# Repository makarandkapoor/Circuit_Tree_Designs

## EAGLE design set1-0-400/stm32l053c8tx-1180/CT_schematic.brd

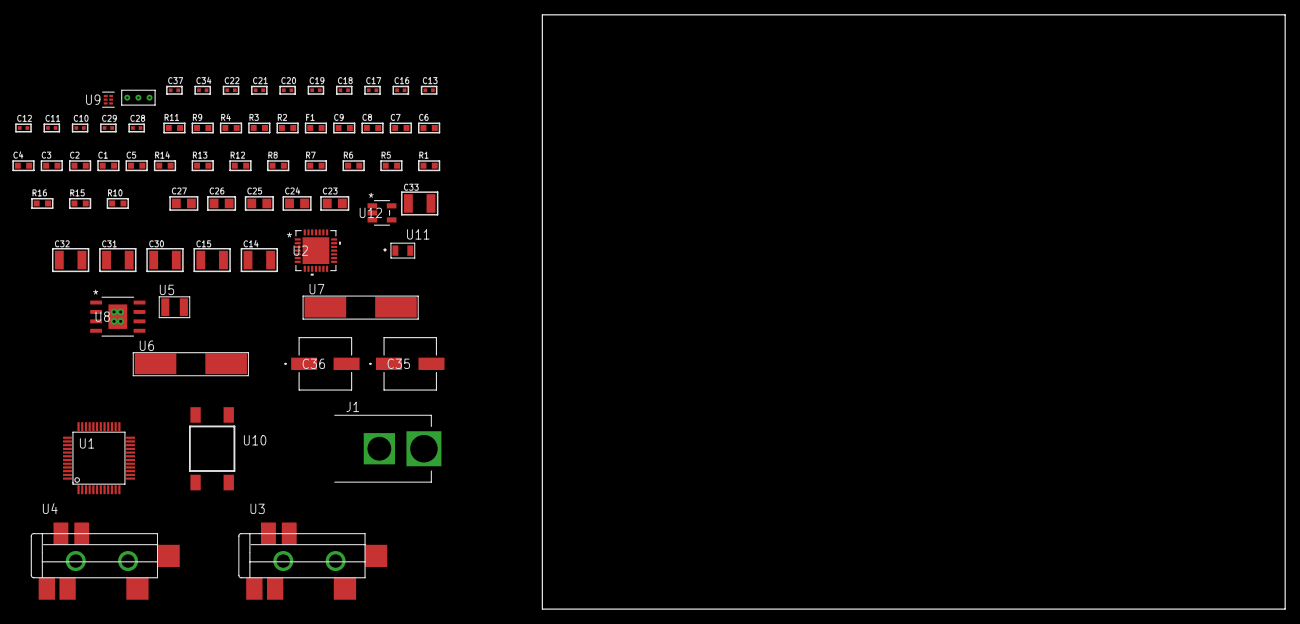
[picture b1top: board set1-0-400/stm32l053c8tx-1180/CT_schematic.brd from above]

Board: 2 copper layers, 100.0 x 80.0 mm, 68 parts (0 on the bottom side), 29 nets, no tracks yet.

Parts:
C1, C2, C3, C4, C6, C9: 1e-07; C0603
C5: 4.7e-06; C0603
C7: 1e-08; C0603
C8: 1e-06; C0603
C10, C11, C12, C13: 1e-11; C0402
C14, C15: 2.2e-05; C1210
C16, C17: 1e-09; C0402
C18, C19, C20, C21, C22, C34: 1e-07; C0402
C23, C24, C25, C26, C27: 1e-05; C0805
C28, C29: 2.2e-11; C0402
C30, C31, C32, C33: 1e-05; C1210
C35, C36: 0.0001; EXV-9H
C37: 1e-08; C0402
F1: 240.0; L0603
J1: PJ-037B; PJ-037B_PACKAGE
R1, R5, R12, R13: 10000.0; R0603
R2: 1000.0; R0603
R3: 910.0; R0603
R4: 4700.0; R0603
R6, R7, R8: 47000.0; R0603
R9: 680.0; R0603
R10: 1402.2764227642; R0603
R11: 2200.0; R0603
R14: 82000.0; R0603
R15: 300000.0; R0603
R16: 120000.0; R0603
U1: STM32L053C8T7; LQFP48
U2: WM8731CLSEFL; QFN-28
U3, U4: SJ-43515TS-SMT-TR
U5: ABS07-32.768KHZ-7-T
U6: ABLS-25.000MHZ-B2F-T
U7: ABLS-12.288MHZ-B4-T
U8: MIC5234YME; SOIC-8_EP
U9: TPS3895ADRYR; SON-6
U10: 4-1437565-2; SW_4-1437565-2
U11: Q65110A2395; LGM67K-G1J2-24-Z
U12: nc7sz125m5x; NC7SZ125M5X
U13: Dummy; DUMMY_PACKAGE_130

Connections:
CLK_CRYSTAL_U1_3: C10.1, U1.3, U5.1
CLK_CRYSTAL_U1_4: C11.1, U1.4, U5.2
CLK_CRYSTAL_U1_5: C12.1, U1.5, U6.1
CLK_CRYSTAL_U1_6: C13.1, U1.6, U6.2
CLK_CRYSTAL_U2_1: C28.1, U2.1, U7.1
CLK_CRYSTAL_U2_2: C29.1, U2.2, U7.2
GND: C1.2, C2.2, C3.2, C4.2, C5.2, C6.2, C7.2, C8.2, C9.2, C10.2, C11.2, C12.2, C13.2, C17.2, C18.2, C19.2, C20.2, C21.2, C22.2, C23.2, C24.2, C25.2, C26.2, C27.2, C28.2, C29.2, C30.2, C31.2, C32.2, C33.2, C34.2, C35.2, C36.2, C37.2, J1.2, R2.2, R5.2, R6.2, R7.2, R8.2, R11.2, R14.2, R16.2, U1.8, U1.23, U1.35, U1.47, U2.4, U2.15, U2.19, U2.25, U2.26, U2.29, U3.1, U4.1, U8.7, U8.EPAD, U9.2, U11.C, U12.1, U12.3, U13.1
NET_U1_1: C6.1, U1.1
NET_U1_7: R4.1, U1.7, U12.4
NET_U1_9: C7.1, C8.1, F1.1, U1.9
NET_U1_44: R5.1, U1.44
NET_U1_45: R3.1, U1.45, U11.A
NET_U1_46: R1.1, U1.46, U10.3, U10.4
NET_U2_20: C22.1, C27.1, U2.20
NET_U3_2: C15.1, R7.1, U3.2
NET_U3_5: C14.1, R6.1, U3.5
NET_U4_5: C16.1, C17.1, R8.1, R9.1, U4.5
NET_U8_4: R10.2, R11.1, U8.4
NET_U9_1: R13.1, R14.1, U9.1
NET_U9_3: R15.2, R16.1, U9.3
NET_U9_4: R12.1, U9.4, U12.2
NET_U10_1: R2.1, U10.1, U10.2
PROC_I2S2_CK: U1.26, U2.7
PROC_I2S2_SD: U1.28, U2.8
PROC_I2S2_WS: U1.25, U2.9, U2.11
PROC_TIM2_CH1: U1.10, U13.3
PROC_TIM2_CH3: U1.12, U13.2
VCC_S1_4V6: C30.1, C31.1, C35.1, C36.1, J1.1, U8.5, U8.8
VCC_TIER1_1V8: C1.1, C2.1, C3.1, C4.1, C5.1, C9.1, C18.1, C19.1, C20.1, C21.1, C23.1, C24.1, C25.1, C26.1, C32.1, C33.1, C34.1, C37.1, F1.2, R1.2, R3.2, R4.2, R10.1, R12.2, R13.2, R15.1, U1.24, U1.36, U1.48, U2.3, U2.5, U2.12, U2.18, U8.1, U9.6, U12.5

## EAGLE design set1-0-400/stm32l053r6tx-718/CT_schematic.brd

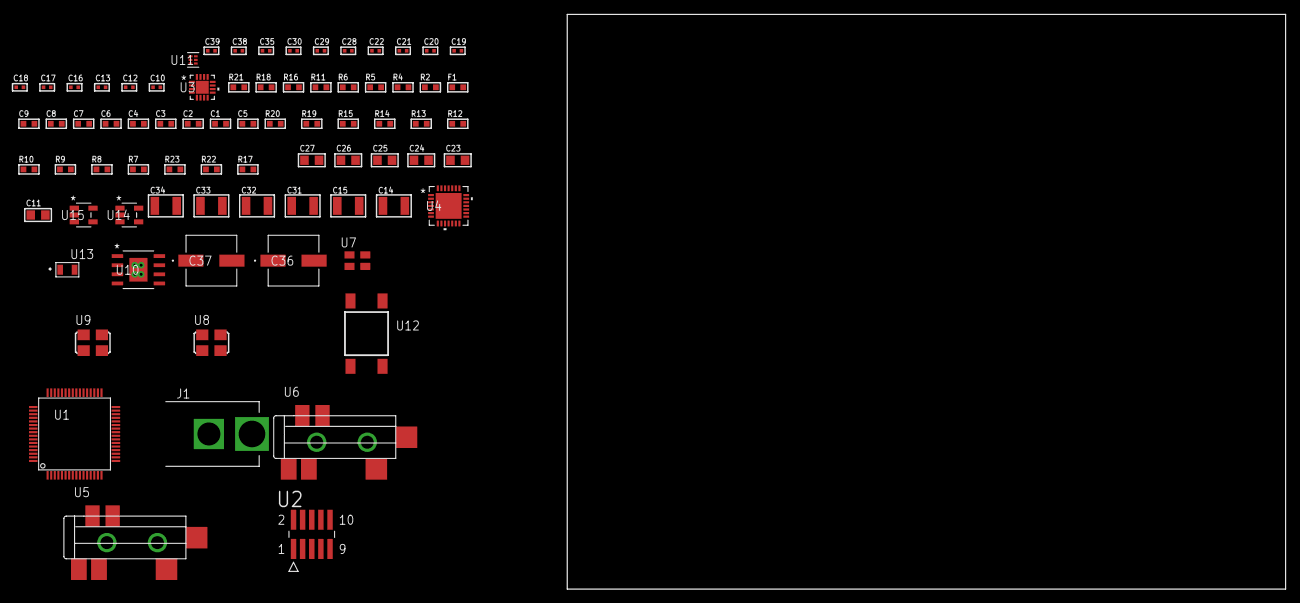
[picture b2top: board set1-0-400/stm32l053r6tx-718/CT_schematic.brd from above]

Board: 2 copper layers, 100.0 x 80.0 mm, 77 parts (0 on the bottom side), 31 nets, no tracks yet.

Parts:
C1, C2, C3, C4, C6, C9: 1e-07; C0603
C5: 4.7e-06; C0603
C7: 1e-08; C0603
C8: 1e-06; C0603
C10, C12, C13, C18, C19, C20, C21, C22, C35: 1e-07; C0402
C11: 4.7e-06; C0805
C14, C15: 2.2e-05; C1210
C16, C17: 1e-09; C0402
C23, C24, C25, C26, C27: 1e-05; C0805
C28, C29, C30, C38, C39: 1e-08; C0402
C31, C32, C33, C34: 1e-05; C1210
C36, C37: 0.0001; EXV-9H
F1: 240.0; L0603
J1: PJ-037B; PJ-037B_PACKAGE
R2: 1000.0; R0603
R4: 4700.0; R0603
R5, R6, R18: 2200.0; R0603
R7, R8, R9, R10, R12, R19, R20: 10000.0; R0603
R11: 5.0; R0603
R13, R14, R15: 47000.0; R0603
R16: 680.0; R0603
R17: 4031.5447154472; R0603
R21: 9100.0; R0603
R22: 680000.0; R0603
R23: 120000.0; R0603
U1: STM32L053R6T6; LQFP64
U2: FTSH-105-01-L-DV-K; SAMTEC_FTSH-105-01-L-DV-K
U3: MMA8451QT; QFN-16
U4: WM8731CLSEFL; QFN-28
U5, U6: SJ-43515TS-SMT-TR
U7: ASEK-32.768KHz-ECST; ASEK
U8: ASFL1-12.288MHZ-EC-T; ASFL1
U9: ASFL1-25MHZ-NCS; ASFL1
U10: MIC5234YME; SOIC-8_EP
U11: TPS3895ADRYR; SON-6
U12: 4-1437565-2; SW_4-1437565-2
U13: Q65110A2395; LGM67K-G1J2-24-Z
U14, U15: nc7sz125m5x; NC7SZ125M5X

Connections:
CLK_U1_3: U1.3, U7.3
CLK_U1_5: U1.5, U9.3
CLK_U4_1: U4.1, U8.3
GND: C1.2, C2.2, C3.2, C4.2, C5.2, C6.2, C7.2, C8.2, C9.2, C10.2, C11.2, C12.2, C13.2, C17.2, C18.2, C19.2, C20.2, C21.2, C22.2, C23.2, C24.2, C25.2, C26.2, C27.2, C28.2, C29.2, C30.2, C31.2, C32.2, C33.2, C34.2, C35.2, C36.2, C37.2, C38.2, C39.2, J1.2, R2.2, R7.2, R11.2, R13.2, R14.2, R15.2, R18.2, R21.2, R23.2, U1.12, U1.18, U1.31, U1.47, U1.63, U2.3, U2.5, U3.5, U3.10, U3.12, U3.17, U4.4, U4.15, U4.19, U4.25, U4.26, U4.29, U5.1, U6.1, U7.2, U8.2, U9.2, U10.7, U10.EPAD, U11.2, U13.C, U14.2, U14.3, U15.1, U15.3
NET_U1_1: C6.1, U1.1
NET_U1_7: R4.1, U1.7, U15.4
NET_U1_13: C7.1, C8.1, F1.1, U1.13
NET_U1_58: R5.1, U1.58, U3.4
NET_U1_59: R6.1, U1.59, U3.6
NET_U1_60: R7.1, U1.60
NET_U1_62: U12.3, U12.4
NET_U2_9: R11.1, U2.9
NET_U3_2: C13.1, U3.2
NET_U3_7: R12.1, U3.7
NET_U4_20: C22.1, C27.1, U4.20
NET_U5_2: C15.1, R14.1, U5.2
NET_U5_5: C14.1, R13.1, U5.5
NET_U6_5: C16.1, C17.1, R15.1, R16.1, U6.5
NET_U10_4: R17.2, R18.1, U10.4
NET_U11_1: R20.1, R21.1, U11.1
NET_U11_3: R22.2, R23.1, U11.3
NET_U11_4: R19.1, U11.4, U14.4, U15.2
NET_U12_1: R2.1, U12.1, U12.2
PROC_I2S2_CK: U1.34, U4.7
PROC_I2S2_SD: U1.11, U4.8
PROC_I2S2_WS: U1.33, U4.9, U4.11
PROC_SYS_SWCLK: R9.1, U1.49, U2.4
PROC_SYS_SWDIO: R10.1, U1.46, U2.2
RST_OUT_U2_JTAG_RST_B: R8.1, U2.10, U14.1
VCC_S1_13V3: C31.1, C32.1, C36.1, C37.1, J1.1, U10.5, U10.8
VCC_TIER1_3V3: C1.1, C2.1, C3.1, C4.1, C5.1, C9.1, C10.1, C11.1, C12.1, C18.1, C19.1, C20.1, C21.1, C23.1, C24.1, C25.1, C26.1, C28.1, C29.1, C30.1, C33.1, C34.1, C35.1, C38.1, C39.1, F1.2, R4.2, R5.2, R6.2, R8.2, R9.2, R10.2, R12.2, R17.1, R19.2, R20.2, R22.1, U1.19, U1.32, U1.48, U1.64, U2.1, U3.1, U3.14, U4.3, U4.5, U4.12, U4.18, U7.4, U8.4, U9.4, U10.1, U11.6, U14.5, U15.5

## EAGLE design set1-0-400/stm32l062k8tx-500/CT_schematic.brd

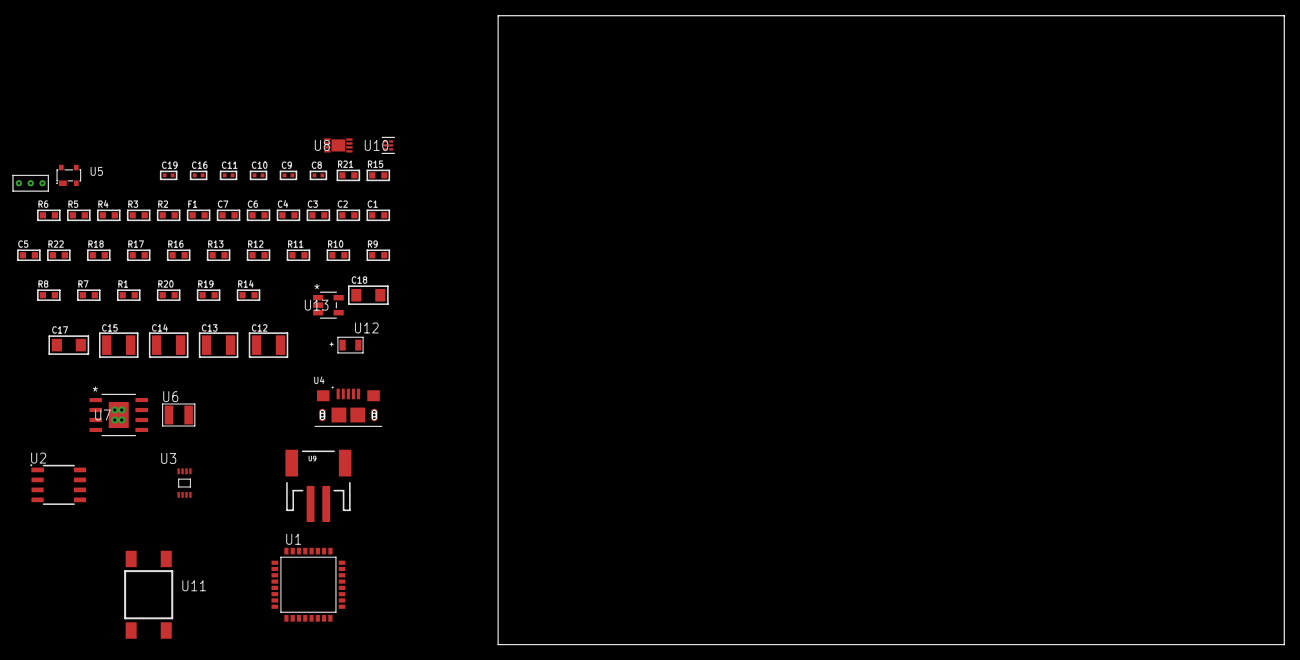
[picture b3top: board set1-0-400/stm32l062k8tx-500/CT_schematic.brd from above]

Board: 2 copper layers, 122.6 x 80.0 mm, 56 parts (0 on the bottom side), 33 nets, no tracks yet.

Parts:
C1, C2, C3, C4: 1e-07; C0603
C5: 4.7e-06; C0603
C6: 1e-08; C0603
C7: 1e-06; C0603
C8, C9: 1e-11; C0402
C10, C11, C19: 1e-08; C0402
C12, C13, C14, C15: 1e-05; C1210
C16: 1e-07; C0402
C17, C18: 1e-05; C1206
F1: 240.0; L0603
R1, R7, R8, R9, R10, R11, R12, R13, R16, R17, R22: 10000.0; R0603
R2: 1000.0; R0603
R3: 910.0; R0603
R4: 4700.0; R0603
R5, R6, R15: 2200.0; R0603
R14: 1402.2764227642; R0603
R18: 82000.0; R0603
R19: 300000.0; R0603
R20: 120000.0; R0603
R21: 2000.0; R0603
U1: STM32L062K8T6; LQFP32
U2: AT25080B-SSHL-T; SOIC-8
U3: 24AA128T-I/MNY; TDFN-8/6MM
U4: 10118193-0001LF; FCI_10118193-0001LF
U5: prtr5v0u2ax; SOT143B
U6: ABS07-32.768KHZ-7-T
U7: MIC5234YME; SOIC-8_EP
U8: MCP73831T-2ACI/MC; DFN8_2X3MC
U9: S2B-PH-SM4-TB(LF)(SN); JST-2-SMD
U10: TPS3895ADRYR; SON-6
U11: 4-1437565-2; SW_4-1437565-2
U12: Q65110A2395; LGM67K-G1J2-24-Z
U13: nc7sz125m5x; NC7SZ125M5X
U14: Dummy; DUMMY_PACKAGE_118

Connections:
CLK_CRYSTAL_U1_2: C8.1, U1.2, U6.1
CLK_CRYSTAL_U1_3: C9.1, U1.3, U6.2
GND: C1.2, C2.2, C3.2, C4.2, C5.2, C6.2, C7.2, C8.2, C9.2, C10.2, C11.2, C12.2, C13.2, C14.2, C15.2, C16.2, C17.2, C18.2, C19.2, R2.2, R7.2, R11.2, R15.2, R18.2, R20.2, R21.2, U1.16, U1.32, U2.4, U3.4, U4.5, U4.6, U4.7, U4.8, U4.9, U5.1, U7.7, U7.EPAD, U8.6, U8.9, U9.2, U10.2, U12.C, U13.1, U13.3, U14.1
INPUT_USBPOWER_5V: C17.1, R22.2, U4.1, U5.4, U8.1, U8.2
NET_U1_4: R4.1, U1.4, U13.4
NET_U1_5: C6.1, C7.1, F1.1, U1.5
NET_U1_27: R3.1, U1.27, U12.A
NET_U1_28: R1.1, U1.28, U11.3, U11.4
NET_U1_29: R5.1, U1.29, U3.6
NET_U1_30: R6.1, U1.30, U3.5
NET_U1_31: R7.1, U1.31
NET_U2_3: R8.1, U2.3
NET_U2_7: R10.1, U2.7
NET_U3_1: R11.1, U3.1
NET_U3_2: R12.1, U3.2
NET_U3_3: R13.1, U3.3
NET_U7_4: R14.2, R15.1, U7.4
NET_U8_5: R22.1, U8.5
NET_U8_8: R21.1, U8.8
NET_U10_1: R17.1, R18.1, U10.1
NET_U10_3: R19.2, R20.1, U10.3
NET_U10_4: R16.1, U10.4, U13.2
NET_U11_1: R2.1, U11.1, U11.2
PROC_PA0: U1.6, U14.2
PROC_PA1: U1.7, U14.3
PROC_SPI1_MISO: U1.12, U2.2
PROC_SPI1_MOSI: U1.13, U2.5
PROC_SPI1_NSS: R9.1, U1.10, U2.1
PROC_SPI1_SCK: U1.11, U2.6
PROC_USB_DM: U1.21, U4.2, U5.3
PROC_USB_DP: U1.22, U4.3, U5.2
VCC_S1_3V7: C12.1, C13.1, C18.1, U7.5, U7.8, U8.3, U8.4, U9.1
VCC_TIER1_1V8: C1.1, C2.1, C3.1, C4.1, C5.1, C10.1, C11.1, C14.1, C15.1, C16.1, C19.1, F1.2, R1.2, R3.2, R4.2, R5.2, R6.2, R8.2, R9.2, R10.2, R12.2, R13.2, R14.1, R16.2, R17.2, R19.1, U1.1, U1.17, U2.8, U3.7, U3.8, U7.1, U10.6, U13.5

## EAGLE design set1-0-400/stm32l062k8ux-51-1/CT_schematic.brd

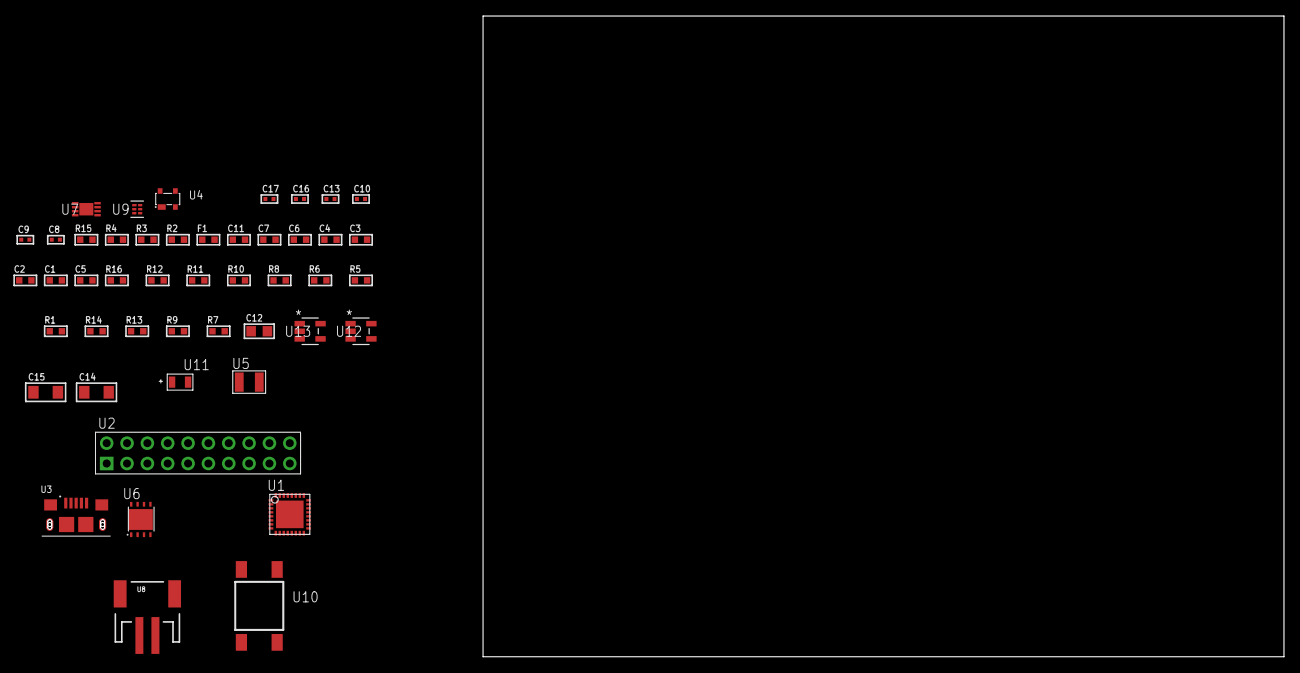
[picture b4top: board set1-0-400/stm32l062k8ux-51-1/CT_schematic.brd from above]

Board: 2 copper layers, 154.3 x 80.0 mm, 47 parts (0 on the bottom side), 24 nets, no tracks yet.

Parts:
C1, C2, C3, C4: 1e-07; C0603
C5: 4.7e-06; C0603
C6: 1e-08; C0603
C7, C11: 1e-06; C0603
C8, C9: 1e-11; C0402
C10, C13: 1e-07; C0402
C12: 1e-05; C0805
C14, C15: 1e-05; C1206
C16, C17: 1e-08; C0402
F1: 240.0; L0603
R1, R5, R6, R10, R11, R16: 10000.0; R0603
R2: 1000.0; R0603
R3: 910.0; R0603
R4: 4700.0; R0603
R7, R9: 100000.0; R0603
R8: 36000.0; R0603
R12: 82000.0; R0603
R13: 300000.0; R0603
R14: 120000.0; R0603
R15: 2000.0; R0603
U1: STM32L062K8U6; UFQFPN32
U2: TST-110-05-T-D-RA
U3: 10118193-0001LF; FCI_10118193-0001LF
U4: prtr5v0u2ax; SOT143B
U5: ABS07-32.768KHZ-7-T
U6: LP2951ACSDX/NOPB; WSON-8
U7: MCP73831T-2ACI/MC; DFN8_2X3MC
U8: S2B-PH-SM4-TB(LF)(SN); JST-2-SMD
U9: TPS3895ADRYR; SON-6
U10: 4-1437565-2; SW_4-1437565-2
U11: Q65110A2395; LGM67K-G1J2-24-Z
U12, U13: nc7sz125m5x; NC7SZ125M5X

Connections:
CLK_CRYSTAL_U1_2: C8.1, U1.2, U5.1
CLK_CRYSTAL_U1_3: C9.1, U1.3, U5.2
GND: C1.2, C2.2, C3.2, C4.2, C5.2, C6.2, C7.2, C8.2, C9.2, C10.2, C11.2, C12.2, C13.2, C14.2, C15.2, C16.2, C17.2, R2.2, R5.2, R9.2, R12.2, R14.2, R15.2, U1.EPAD, U2.4, U2.6, U2.8, U2.10, U2.12, U2.14, U2.16, U2.18, U2.20, U3.5, U3.6, U3.7, U3.8, U3.9, U4.1, U6.3, U6.4, U6.PAD, U7.6, U7.9, U8.2, U9.2, U11.C, U12.2, U12.3, U13.1, U13.3
INPUT_USBPOWER_5V: C14.1, R16.2, U3.1, U4.4, U7.1, U7.2
NET_U1_4: R4.1, U1.4, U13.4
NET_U1_5: C6.1, C7.1, F1.1, U1.5
NET_U1_30: R3.1, U1.30, U11.A
NET_U1_31: R5.1, U1.31
NET_U1_32: R1.1, U1.32, U10.3, U10.4
NET_U6_5: R7.1, U6.5
NET_U6_7: R8.2, R9.1, U6.7
NET_U7_5: R16.1, U7.5
NET_U7_8: R15.1, U7.8
NET_U9_1: R11.1, R12.1, U9.1
NET_U9_3: R13.2, R14.1, U9.3
NET_U9_4: R10.1, U9.4, U12.4, U13.2
NET_U10_1: R2.1, U10.1, U10.2
PROC_SYS_SWCLK: U1.24, U2.9
PROC_SYS_SWDIO: U1.23, U2.7
PROC_USB_DM: U1.21, U3.2, U4.3
PROC_USB_DP: U1.22, U3.3, U4.2
RST_OUT_U2_SRESET_B: R6.1, U2.15, U12.1
VCC_S1_3V7: C11.1, C15.1, U6.8, U7.3, U7.4, U8.1
VCC_TIER1_1V8: C1.1, C2.1, C3.1, C4.1, C5.1, C10.1, C12.1, C13.1, C16.1, C17.1, F1.2, R1.2, R3.2, R4.2, R6.2, R7.2, R8.1, R10.2, R11.2, R13.1, U1.1, U1.17, U2.1, U6.1, U9.6, U12.5, U13.5

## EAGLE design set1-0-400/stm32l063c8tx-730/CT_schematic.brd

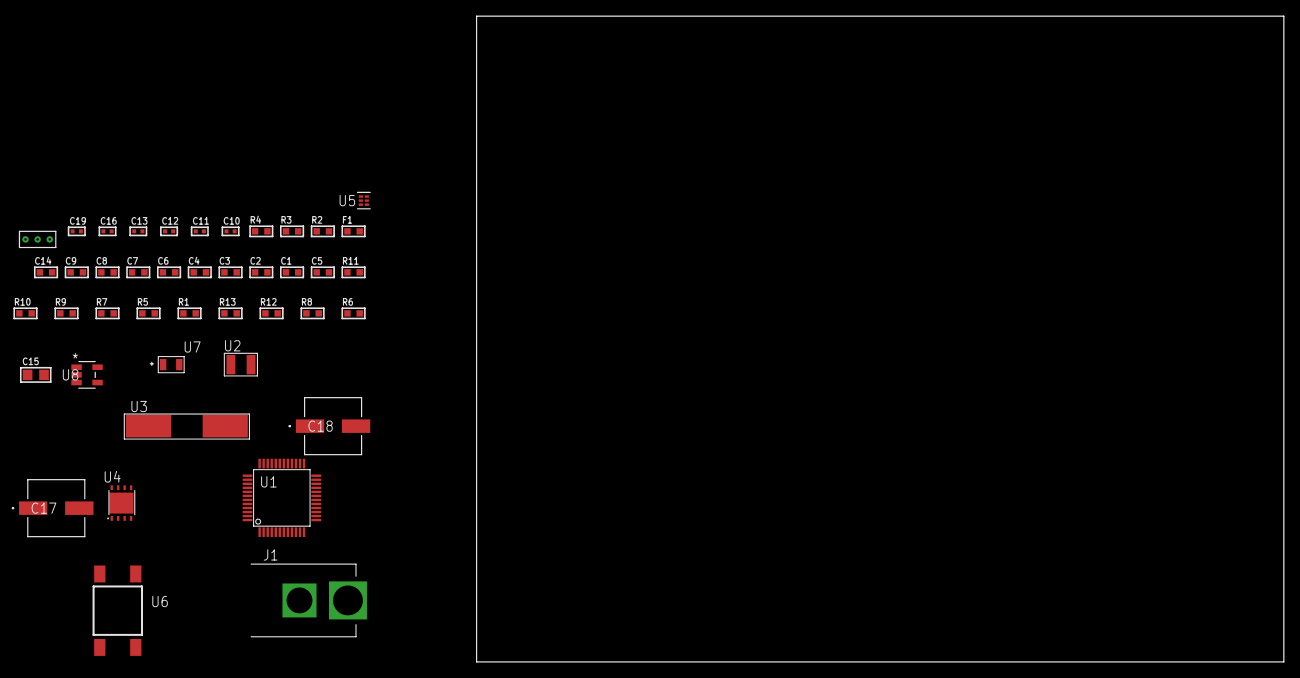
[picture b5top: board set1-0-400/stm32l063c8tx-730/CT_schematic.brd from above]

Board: 2 copper layers, 100.0 x 80.0 mm, 43 parts (0 on the bottom side), 21 nets, no tracks yet.

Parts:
C1, C2, C3, C4, C6, C9: 1e-07; C0603
C5: 4.7e-06; C0603
C7: 1e-08; C0603
C8: 1e-06; C0603
C10, C11, C12, C13: 1e-11; C0402
C14: 8e-07; R0603
C15: 1e-05; C0805
C16: 1e-07; C0402
C17, C18: 0.0001; EXV-9H
C19: 1e-08; C0402
F1: 240.0; L0603
J1: PJ-037B; PJ-037B_PACKAGE
R1, R5, R9, R10: 10000.0; R0603
R2: 1000.0; R0603
R3: 910.0; R0603
R4: 4700.0; R0603
R6, R8: 100000.0; R0603
R7: 36000.0; R0603
R11: 82000.0; R0603
R12: 300000.0; R0603
R13: 120000.0; R0603
U1: STM32L063C8T6; LQFP48
U2: ABS07-32.768KHZ-7-T
U3: ABLS-25.000MHZ-B2F-T
U4: LP2951ACSDX/NOPB; WSON-8
U5: TPS3895ADRYR; SON-6
U6: 4-1437565-2; SW_4-1437565-2
U7: Q65110A2395; LGM67K-G1J2-24-Z
U8: nc7sz125m5x; NC7SZ125M5X
U9: Dummy; DUMMY_PACKAGE_84

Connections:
CLK_CRYSTAL_U1_3: C10.1, U1.3, U2.1
CLK_CRYSTAL_U1_4: C11.1, U1.4, U2.2
CLK_CRYSTAL_U1_5: C12.1, U1.5, U3.1
CLK_CRYSTAL_U1_6: C13.1, U1.6, U3.2
GND: C1.2, C2.2, C3.2, C4.2, C5.2, C6.2, C7.2, C8.2, C9.2, C10.2, C11.2, C12.2, C13.2, C14.2, C15.2, C16.2, C17.2, C18.2, C19.2, J1.2, R2.2, R5.2, R8.2, R11.2, R13.2, U1.8, U1.23, U1.35, U1.47, U4.3, U4.4, U4.PAD, U5.2, U7.C, U8.1, U8.3, U9.1
NET_U1_1: C6.1, U1.1
NET_U1_7: R4.1, U1.7, U8.4
NET_U1_9: C7.1, C8.1, F1.1, U1.9
NET_U1_44: R5.1, U1.44
NET_U1_45: R3.1, U1.45, U7.A
NET_U1_46: R1.1, U1.46, U6.3, U6.4
NET_U4_5: R6.1, U4.5
NET_U4_7: R7.2, R8.1, U4.7
NET_U5_1: R10.1, R11.1, U5.1
NET_U5_3: R12.2, R13.1, U5.3
NET_U5_4: R9.1, U5.4, U8.2
NET_U6_1: R2.1, U6.1, U6.2
PROC_PA0: U1.10, U9.3
PROC_PC13: U1.2, U9.2
VCC_S1_13V5: C14.1, C17.1, C18.1, J1.1, U4.8
VCC_TIER1_1V8: C1.1, C2.1, C3.1, C4.1, C5.1, C9.1, C15.1, C16.1, C19.1, F1.2, R1.2, R3.2, R4.2, R6.2, R7.1, R9.2, R10.2, R12.1, U1.24, U1.36, U1.48, U4.1, U5.6, U8.5

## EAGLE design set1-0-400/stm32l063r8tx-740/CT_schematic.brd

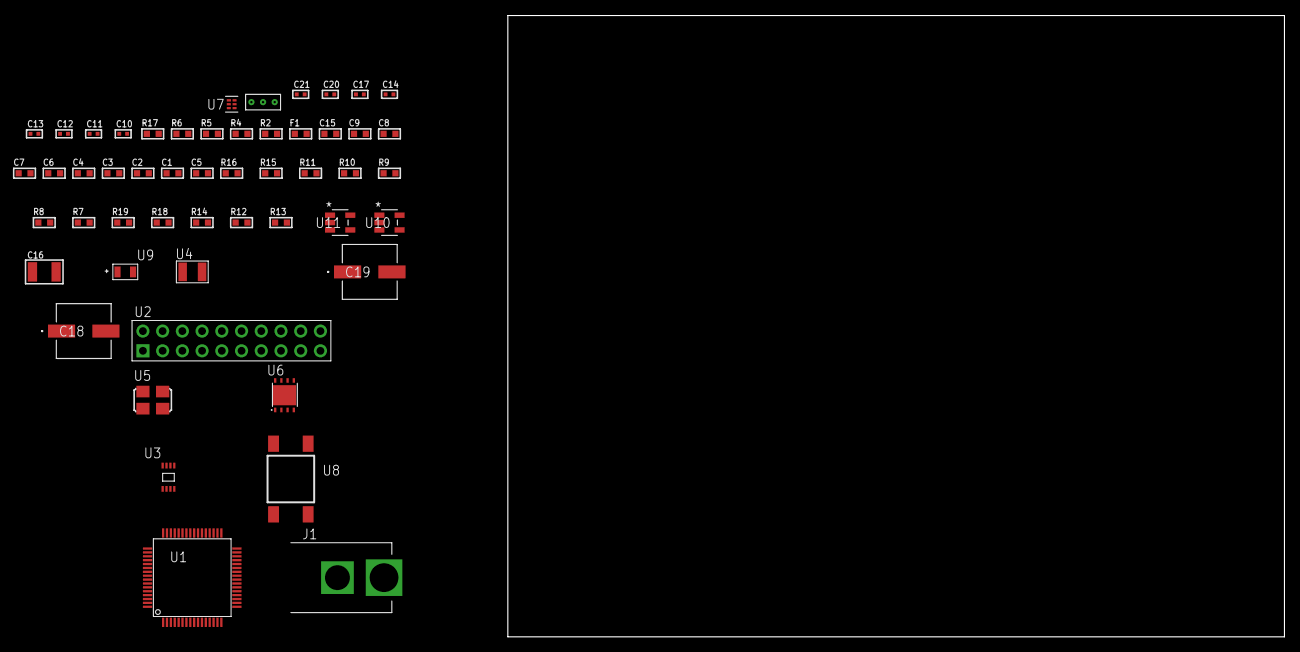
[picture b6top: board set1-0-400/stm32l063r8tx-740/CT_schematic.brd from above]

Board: 2 copper layers, 100.0 x 80.0 mm, 52 parts (0 on the bottom side), 27 nets, no tracks yet.

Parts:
C1, C2, C3, C4, C6, C9: 1e-07; C0603
C5: 4.7e-06; C0603
C7: 1e-08; C0603
C8: 1e-06; C0603
C10, C11: 1e-11; C0402
C12, C17: 1e-07; C0402
C13, C14, C20, C21: 1e-08; C0402
C15: 8e-07; R0603
C16: 1e-05; C1210
C18, C19: 0.0001; EXV-9H
F1: 240.0; L0603
J1: PJ-037B; PJ-037B_PACKAGE
R2: 1000.0; R0603
R4: 4700.0; R0603
R5, R6: 2200.0; R0603
R7, R8, R9, R10, R11, R15, R16: 10000.0; R0603
R12, R14: 100000.0; R0603
R13: 153694.38; R0603
R17: 9100.0; R0603
R18: 680000.0; R0603
R19: 120000.0; R0603
U1: STM32L063R8T6; LQFP64
U2: TST-110-05-T-D-RA
U3: 24AA128T-I/MNY; TDFN-8/6MM
U4: ABS07-32.768KHZ-7-T
U5: ASFL1-25MHZ-NCS; ASFL1
U6: LP2951ACSDX/NOPB; WSON-8
U7: TPS3895ADRYR; SON-6
U8: 4-1437565-2; SW_4-1437565-2
U9: Q65110A2395; LGM67K-G1J2-24-Z
U10, U11: nc7sz125m5x; NC7SZ125M5X
U12: Dummy; DUMMY_PACKAGE_114

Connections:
CLK_CRYSTAL_U1_3: C10.1, U1.3, U4.1
CLK_CRYSTAL_U1_4: C11.1, U1.4, U4.2
CLK_U1_5: U1.5, U5.3
GND: C1.2, C2.2, C3.2, C4.2, C5.2, C6.2, C7.2, C8.2, C9.2, C10.2, C11.2, C12.2, C13.2, C14.2, C15.2, C16.2, C17.2, C18.2, C19.2, C20.2, C21.2, J1.2, R2.2, R7.2, R10.2, R11.2, R14.2, R17.2, R19.2, U1.12, U1.18, U1.31, U1.47, U1.63, U2.4, U2.6, U2.8, U2.10, U2.12, U2.14, U2.16, U2.18, U2.20, U3.4, U3.7, U5.2, U6.3, U6.4, U6.PAD, U7.2, U9.C, U10.2, U10.3, U11.1, U11.3, U12.1
NET_U1_1: C6.1, U1.1
NET_U1_7: R4.1, U1.7, U11.4
NET_U1_13: C7.1, C8.1, F1.1, U1.13
NET_U1_58: R5.1, U1.58, U3.6
NET_U1_59: R6.1, U1.59, U3.5
NET_U1_60: R7.1, U1.60
NET_U1_62: U8.3, U8.4
NET_U3_1: R9.1, U3.1
NET_U3_2: R10.1, U3.2
NET_U3_3: R11.1, U3.3
NET_U6_5: R12.1, U6.5
NET_U6_7: R13.2, R14.1, U6.7
NET_U7_1: R16.1, R17.1, U7.1
NET_U7_3: R18.2, R19.1, U7.3
NET_U7_4: R15.1, U7.4, U10.4, U11.2
NET_U8_1: R2.1, U8.1, U8.2
PROC_ADC_IN3: U1.17, U12.3
PROC_ADC_IN13: U1.11, U12.2
PROC_SYS_SWCLK: U1.49, U2.9
PROC_SYS_SWDIO: U1.46, U2.7
RST_OUT_U2_SRESET_B: R8.1, U2.15, U10.1
VCC_S1_13V9: C15.1, C18.1, C19.1, J1.1, U6.8
VCC_TIER1_3V3: C1.1, C2.1, C3.1, C4.1, C5.1, C9.1, C12.1, C13.1, C14.1, C16.1, C17.1, C20.1, C21.1, F1.2, R4.2, R5.2, R6.2, R8.2, R9.2, R12.2, R13.1, R15.2, R16.2, R18.1, U1.19, U1.32, U1.48, U1.64, U2.1, U3.8, U5.4, U6.1, U7.6, U10.5, U11.5

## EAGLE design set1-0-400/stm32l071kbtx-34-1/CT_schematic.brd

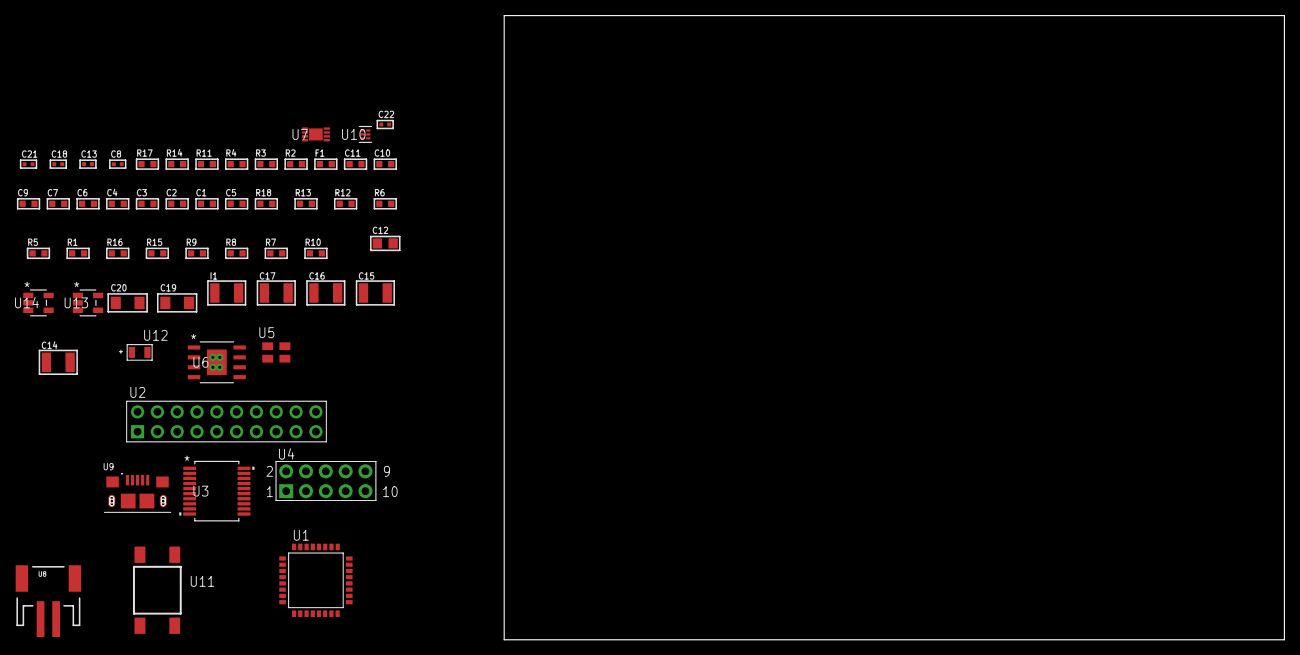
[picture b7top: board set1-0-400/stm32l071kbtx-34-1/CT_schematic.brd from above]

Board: 2 copper layers, 56 parts (0 on the bottom side), 36 nets, no tracks yet.

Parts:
C1, C2, C3, C4: 1e-07; C0603
C5: 4.7e-06; C0603
C6: 1e-08; C0603
C7, C9, C10, C11: 1e-06; C0603
C8, C18: 1e-07; C0402
C12: 4.7e-06; C0805
C13, C21, C22: 1e-08; C0402
C14, C15, C16, C17: 1e-05; C1210
C19, C20: 1e-05; C1206
F1: 240.0; L0603
I1: 1.5e-05; L1210
R1, R5, R6, R12, R13, R18: 10000.0; R0603
R2: 1000.0; R0603
R3: 1600.5; R0603
R4: 4700.0; R0603
R7, R8, R9: 100000.0; R0603
R10: 4031.5447154472; R0603
R11: 2200.0; R0603
R14: 9100.0; R0603
R15: 680000.0; R0603
R16: 120000.0; R0603
R17: 2000.0; R0603
U1: STM32L071KBT6; LQFP32
U2: TST-110-05-T-D-RA
U3: MAX3218EAP+T; SSOP-20
U4: HTSS-105-01-G-D
U5: ASEK-32.768KHz-ECST; ASEK
U6: MIC5234YME; SOIC-8_EP
U7: MCP73831T-2ACI/MC; DFN8_2X3MC
U8: S2B-PH-SM4-TB(LF)(SN); JST-2-SMD
U9: 10118193-0001LF; FCI_10118193-0001LF
U10: TPS3895ADRYR; SON-6
U11: 4-1437565-2; SW_4-1437565-2
U12: Q65110A2395; LGM67K-G1J2-24-Z
U13, U14: nc7sz125m5x; NC7SZ125M5X

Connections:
CLK_U1_2: U1.2, U5.3
GND: C1.2, C2.2, C3.2, C4.2, C5.2, C6.2, C7.2, C8.2, C9.2, C10.2, C11.2, C13.2, C14.2, C15.2, C16.2, C17.2, C18.2, C19.2, C20.2, C21.2, C22.2, R2.2, R5.2, R11.2, R14.2, R16.2, R17.2, U1.16, U1.32, U2.4, U2.6, U2.8, U2.10, U2.12, U2.14, U2.16, U2.18, U2.20, U3.5, U3.17, U3.20, U4.9, U5.2, U6.7, U6.EPAD, U7.6, U7.9, U8.2, U9.5, U9.6, U9.7, U9.8, U9.9, U10.2, U12.C, U13.2, U13.3, U14.1, U14.3
INPUT_USBPOWER_5V: C19.1, R18.2, U7.1, U7.2, U9.1
NET_U1_4: R4.1, U1.4, U14.4
NET_U1_5: C6.1, C7.1, F1.1, U1.5
NET_U1_29: R3.1, U1.29, U12.A
NET_U1_30: R1.1, U1.30, U11.3, U11.4
NET_U1_31: R5.1, U1.31
NET_U3_1: I1.1, U3.1
NET_U3_2: R7.1, U3.2
NET_U3_3: R8.1, U3.3
NET_U3_4: R9.1, U3.4
NET_U3_15: C11.1, U3.15
NET_U3_16: C12.2, U3.16
NET_U3_18: C12.1, U3.18
NET_U3_19: C10.1, U3.19
NET_U4_3: U3.12, U4.3
NET_U4_4: U3.11, U4.4
NET_U4_5: U3.14, U4.5
NET_U4_6: U3.13, U4.6
NET_U6_4: R10.2, R11.1, U6.4
NET_U7_5: R18.1, U7.5
NET_U7_8: R17.1, U7.8
NET_U10_1: R13.1, R14.1, U10.1
NET_U10_3: R15.2, R16.1, U10.3
NET_U10_4: R12.1, U10.4, U13.4, U14.2
NET_U11_1: R2.1, U11.1, U11.2
PROC_LPUART1_CTS: U1.12, U3.8
PROC_LPUART1_RTS: U1.15, U3.10
PROC_LPUART1_RX: U1.9, U3.9
PROC_LPUART1_TX: U1.8, U3.7
PROC_SYS_SWCLK: U1.24, U2.9
PROC_SYS_SWDIO: U1.23, U2.7
RST_OUT_U2_SRESET_B: R6.1, U2.15, U13.1
VCC_S1_3V7: C14.1, C15.1, C20.1, U6.5, U6.8, U7.3, U7.4, U8.1
VCC_TIER1_3V3: C1.1, C2.1, C3.1, C4.1, C5.1, C8.1, C9.1, C13.1, C16.1, C17.1, C18.1, C21.1, C22.1, F1.2, I1.2, R1.2, R3.2, R4.2, R6.2, R7.2, R8.2, R9.2, R10.1, R12.2, R13.2, R15.1, U1.1, U1.17, U2.1, U3.6, U5.4, U6.1, U10.6, U13.5, U14.5

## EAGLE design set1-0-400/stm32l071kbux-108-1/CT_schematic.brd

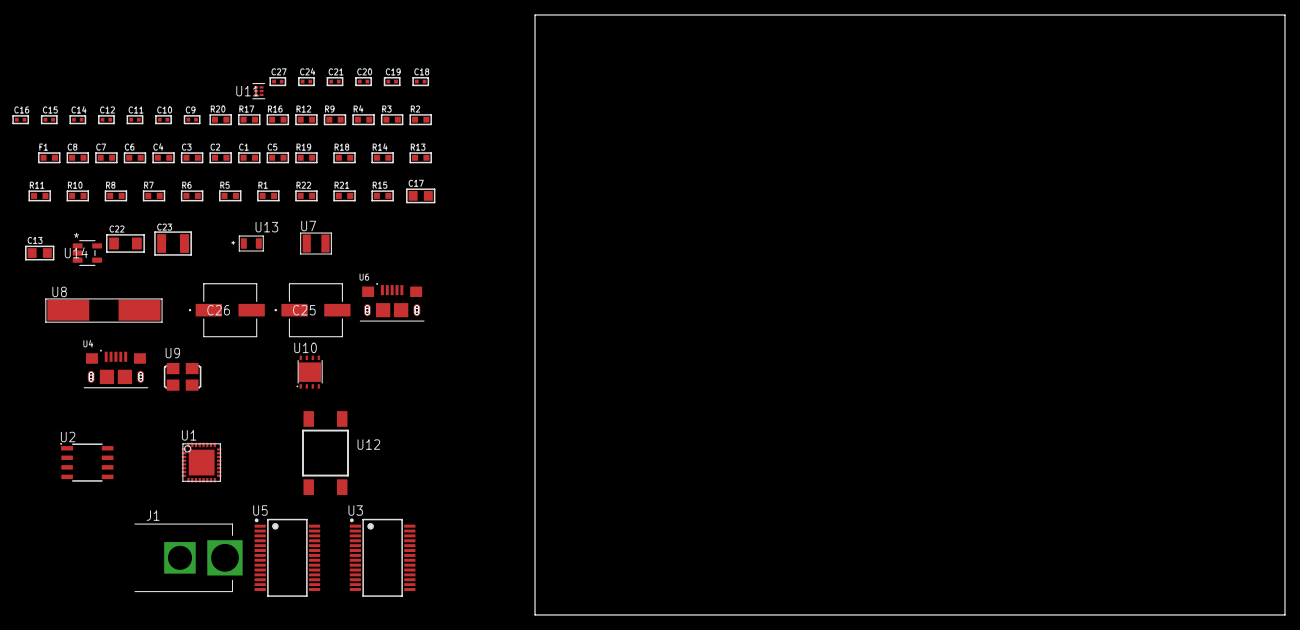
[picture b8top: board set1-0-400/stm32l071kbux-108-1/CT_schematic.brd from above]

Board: 2 copper layers, 159.4 x 80.0 mm, 65 parts (0 on the bottom side), 46 nets, no tracks yet.

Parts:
C1, C2, C3, C4, C6: 1e-07; C0603
C5: 4.7e-06; C0603
C7: 1e-08; C0603
C8: 1e-06; C0603
C9, C10: 1e-11; C0402
C11, C20, C21, C27: 1e-08; C0402
C12, C14, C15, C16, C18, C19, C24: 1e-07; C0402
C13, C17: 4.7e-06; C0805
C22: 1e-05; C1206
C23: 1e-05; C1210
C25, C26: 0.0001; EXV-9H
F1: 240.0; L0603
J1: PJ-037B; PJ-037B_PACKAGE
R1, R5, R6, R7, R8, R10, R11, R13, R14, R18, R19: 10000.0; R0603
R2, R17: 1000.0; R0603
R3: 1600.5; R0603
R4, R9, R12: 4700.0; R0603
R15: 100000.0; R0603
R16: 2231.0; R0603
R20: 9100.0; R0603
R21: 680000.0; R0603
R22: 120000.0; R0603
U1: STM32L071KBU3; UFQFPN32
U2: AT25040B-SSHL-T; SOIC-8
U3, U5: FT232RL-REEL; SSOP-28
U4, U6: 10118193-0001LF; FCI_10118193-0001LF
U7: ABS07-32.768KHZ-7-T
U8: ABLS-12.000MHZ-B4-T
U9: ASFL1-12MHZ-NCS; ASFL1
U10: LP3878SDX-ADJ/NOPB; WSON-8
U11: TPS3895ADRYR; SON-6
U12: 4-1437565-2; SW_4-1437565-2
U13: Q65110A2395; LGM67K-G1J2-24-Z
U14: nc7sz125m5x; NC7SZ125M5X

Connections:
CLK_CRYSTAL_U1_1: C9.1, U1.1, U7.1
CLK_CRYSTAL_U1_2: C10.1, U1.2, U7.2
CLK_CRYSTAL_U5_27: U5.27, U8.1
CLK_CRYSTAL_U5_28: U5.28, U8.2
CLK_U3_27: U3.27, U9.3
GND: C1.2, C2.2, C3.2, C4.2, C5.2, C6.2, C7.2, C8.2, C9.2, C10.2, C11.2, C12.2, C13.2, C14.2, C15.2, C16.2, C17.2, C18.2, C19.2, C20.2, C21.2, C22.2, C23.2, C24.2, C25.2, C26.2, C27.2, J1.2, R2.2, R5.2, R11.2, R14.2, R17.2, R20.2, R22.2, U1.4, U1.16, U1.31, U1.EPAD, U2.4, U3.7, U3.18, U3.21, U3.25, U3.26, U4.5, U4.6, U4.7, U4.8, U4.9, U5.7, U5.18, U5.21, U5.25, U5.26, U6.5, U6.6, U6.7, U6.8, U6.9, U9.2, U10.3, U10.PAD, U11.2, U13.C, U14.1, U14.3
NET_U1_3: R4.1, U1.3, U14.4
NET_U1_5: C7.1, C8.1, F1.1, U1.5
NET_U1_28: R3.1, U1.28, U13.A
NET_U1_29: R1.1, U1.29, U12.3, U12.4
NET_U1_30: R5.1, U1.30
NET_U2_3: R6.1, U2.3
NET_U2_7: R8.1, U2.7
NET_U3_14: R10.1, U3.14
NET_U3_17: C14.1, U3.17
NET_U3_19: R11.1, U3.19
NET_U4_1: R9.1, U4.1
NET_U4_2: U3.16, U4.2
NET_U4_3: U3.15, U4.3
NET_U5_14: R13.1, U5.14
NET_U5_17: C18.1, U5.17
NET_U5_19: R14.1, U5.19
NET_U6_1: R12.1, U6.1
NET_U6_2: U5.16, U6.2
NET_U6_3: U5.15, U6.3
NET_U10_1: C21.1, U10.1
NET_U10_6: R16.2, R17.1, U10.6
NET_U10_8: R15.1, U10.8
NET_U11_1: R19.1, R20.1, U11.1
NET_U11_3: R21.2, R22.1, U11.3
NET_U11_4: R18.1, U11.4, U14.2
NET_U12_1: R2.1, U12.1, U12.2
PROC_LPUART1_CTS: U1.12, U3.3
PROC_LPUART1_RTS: U1.15, U3.11
PROC_LPUART1_RX: U1.9, U3.1
PROC_LPUART1_TX: U1.8, U3.5
PROC_SPI1_MISO: U1.26, U2.2
PROC_SPI1_MOSI: U1.13, U2.5
PROC_SPI1_NSS: R7.1, U1.10, U2.1
PROC_SPI1_SCK: U1.11, U2.6
PROC_USART1_CTS: U1.21, U5.3
PROC_USART1_RTS: U1.22, U5.11
PROC_USART1_RX: U1.20, U5.1
PROC_USART1_TX: U1.19, U5.5
VCC_S1_10V4: C22.1, C25.1, C26.1, J1.1, R15.2, U10.4
VCC_TIER1_3V3: C1.1, C2.1, C3.1, C4.1, C5.1, C6.1, C11.1, C12.1, C13.1, C15.1, C16.1, C17.1, C19.1, C20.1, C23.1, C24.1, C27.1, F1.2, R1.2, R3.2, R4.2, R6.2, R7.2, R8.2, R10.2, R13.2, R16.1, R18.2, R19.2, R21.1, U1.17, U1.24, U1.32, U2.8, U3.4, U3.20, U5.4, U5.20, U9.4, U10.5, U11.6, U14.5
